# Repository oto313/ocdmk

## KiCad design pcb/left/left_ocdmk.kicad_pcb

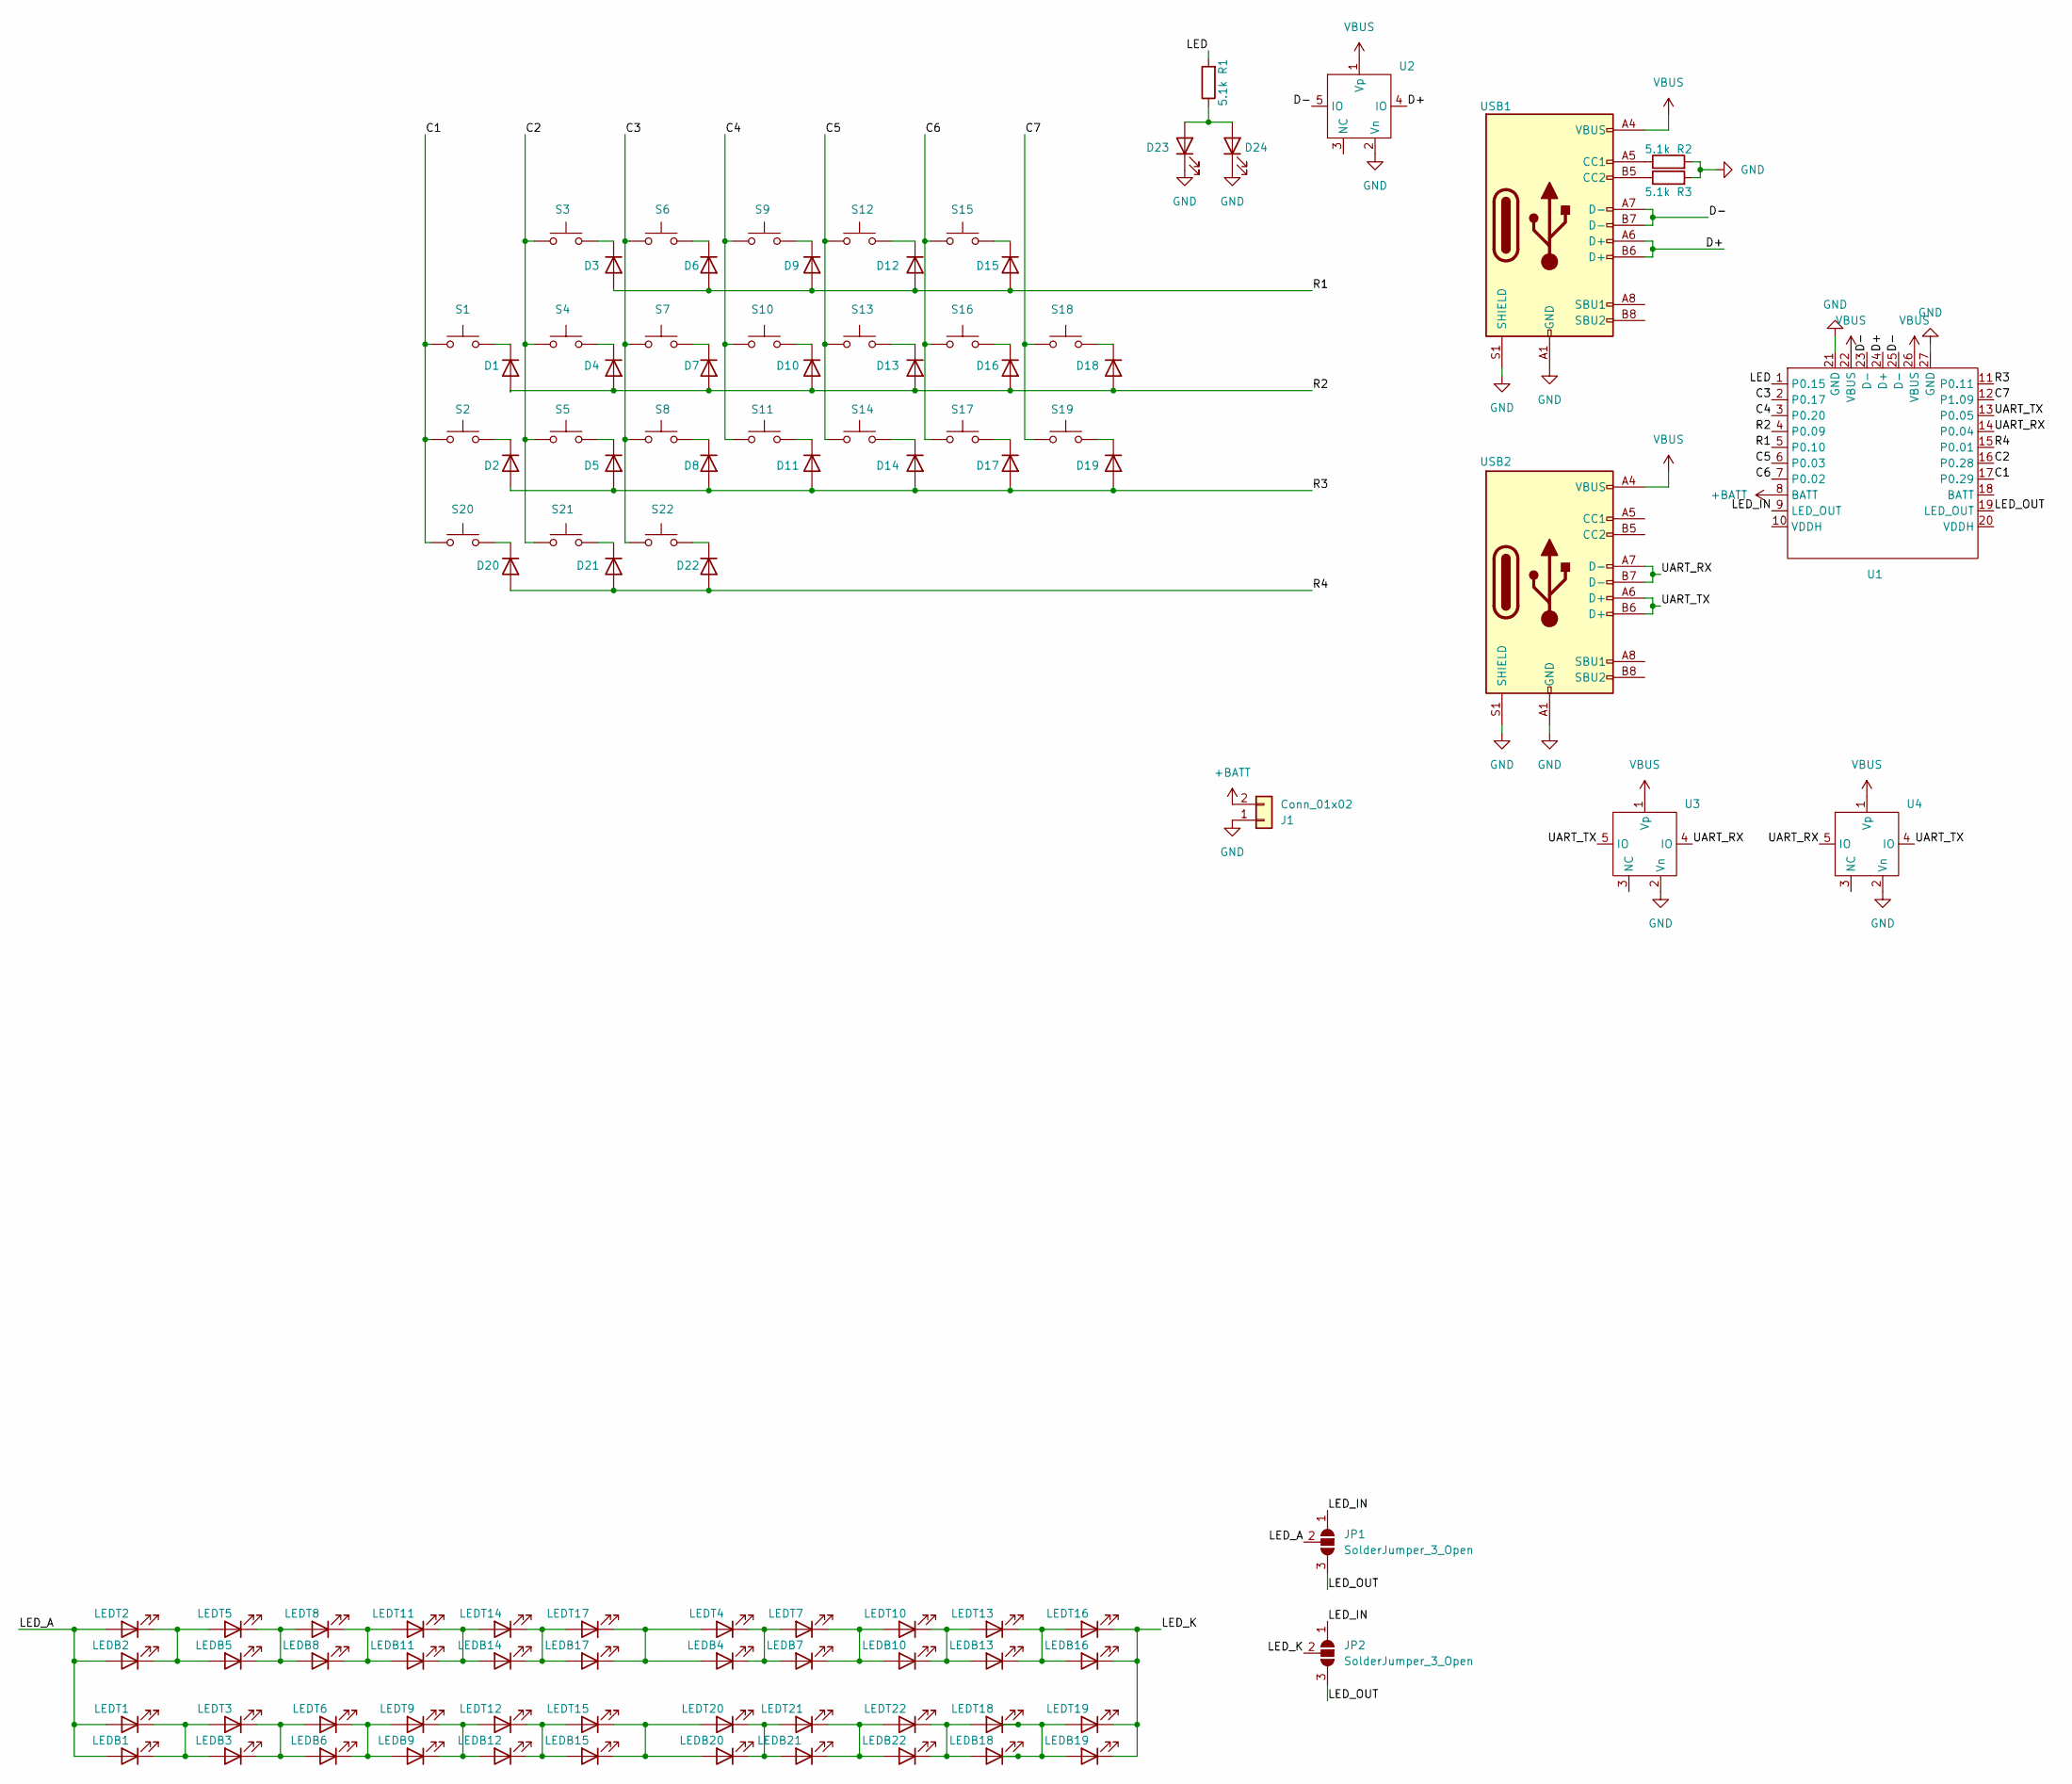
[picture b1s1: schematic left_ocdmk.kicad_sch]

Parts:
D1, D2, D3, D4, D5, D6, D7, D8, D9, D10, D11, D12, D13, D14, D15, D16, D17, D18, D19, D20, D21, D22: diode_tht_sod123_reversible
D23, D24: LED; D_0603_1608Metric
J1: Conn_01x02; JST_PH_S2B-PH-K_1x02_P2.00mm_Horizontal
JP1, JP2: SolderJumper_3_Open; SolderJumper-3_P2.0mm_Open_TrianglePad1.0x1.5mm_NumberLabels
LEDB1, LEDB2, LEDB3, LEDB4, LEDB5, LEDB6, LEDB7, LEDB8, LEDB9, LEDB10, LEDB11, LEDB12, LEDB13, LEDB14, LEDB15, LEDB16, LEDB17, LEDB18, LEDB19, LEDB20, LEDB21, LEDB22: LED_MP-2016-1100-50-90
LEDT1, LEDT2, LEDT3, LEDT4, LEDT5, LEDT6, LEDT7, LEDT8, LEDT9, LEDT10, LEDT11, LEDT12, LEDT13, LEDT14, LEDT15, LEDT16, LEDT17, LEDT18, LEDT19, LEDT20, LEDT21, LEDT22: LED_MP-2016-1100-50-90
R1, R2, R3: 5.1k; R_0603_1608Metric
S1, S2, S3, S4, S5, S6, S7, S8, S9, S10, S11, S12, S13, S14, S15, S16, S17, S18, S19, S20, S21, S22: switch_gateron_ks27_ks33_reversible
U1: ocdmk_core
U2, U3, U4: SOT-553
USB1: USB_C_Receptacle_USB2.0_16P; 12402012E212A_AMP
USB2: USB_C_Receptacle_USB2.0_16P; 12402012E212A_AMP_reversible

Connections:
+BATT: J1.2, U1.8 (BATT)
/C1: S1.1, S2.1, S20.1, U1.17 (P0.29)
/C2: S3.1, S4.1, S5.1, S21.1, U1.16 (P0.28)
/C3: S6.1, S7.1, S8.1, S22.1, U1.2 (P0.17)
/C4: S9.1, S10.1, S11.1, U1.3 (P0.20)
/C5: S12.1, S13.1, S14.1, U1.6 (P0.03)
/C6: S15.1, S16.1, S17.1, U1.7 (P0.02)
/C7: S18.1, S19.1, U1.12 (P1.09)
/D+: U1.24 (D+), U2.4 (IO), USB1.A6 (D+), USB1.B6 (D+)
/D-: U1.23 (D-), U1.25 (D-), U2.5 (IO), USB1.A7 (D-), USB1.B7 (D-)
/LED: R1.2, U1.1 (P0.15)
/LED_A: JP1.2 (C), LEDB1.2 (A), LEDB2.2 (A), LEDT1.2 (A), LEDT2.2 (A)
/LED_IN: JP1.1 (A), JP2.1 (A), U1.9 (LED_OUT)
/LED_K: JP2.2 (C), LEDB16.1 (K), LEDB19.1 (K), LEDT16.1 (K), LEDT19.1 (K)
/LED_OUT: JP1.3 (B), JP2.3 (B), U1.19 (LED_OUT)
/R1: D3.2 (A), D6.2 (A), D9.2 (A), D12.2 (A), D15.2 (A), U1.5 (P0.10)
/R2: D1.2 (A), D4.2 (A), D7.2 (A), D10.2 (A), D13.2 (A), D16.2 (A), D18.2 (A), U1.4 (P0.09)
/R3: D2.2 (A), D5.2 (A), D8.2 (A), D11.2 (A), D14.2 (A), D17.2 (A), D19.2 (A), U1.11 (P0.11)
/R4: D20.2 (A), D21.2 (A), D22.2 (A), U1.15 (P0.01)
/UART_RX: U1.14 (P0.04), U3.4 (IO), U4.5 (IO), USB2.A7 (D-), USB2.B7 (D-)
/UART_TX: U1.13 (P0.05), U3.5 (IO), U4.4 (IO), USB2.A6 (D+), USB2.B6 (D+)
GND: D23.1 (K), D24.1 (K), J1.1, R2.2, R3.2, U1.21 (GND), U1.27 (GND), U2.2 (Vn), U3.2 (Vn), U4.2 (Vn), USB1.A1 (GND), USB1.A12 (GND), USB1.B1 (GND), USB1.B12 (GND), USB1.S1 (SHIELD), USB2.A1 (GND), USB2.A12 (GND), USB2.B1 (GND), USB2.B12 (GND), USB2.S1 (SHIELD)
unnamed: D1.1 (K), S1.2
unnamed: D2.1 (K), S2.2
unnamed: D3.1 (K), S3.2
unnamed: D4.1 (K), S4.2
unnamed: D5.1 (K), S5.2
unnamed: D6.1 (K), S6.2
unnamed: D7.1 (K), S7.2
unnamed: D8.1 (K), S8.2
unnamed: D9.1 (K), S9.2
unnamed: D10.1 (K), S10.2
unnamed: D11.1 (K), S11.2
unnamed: D12.1 (K), S12.2
unnamed: D13.1 (K), S13.2
unnamed: D14.1 (K), S14.2
unnamed: D15.1 (K), S15.2
unnamed: D16.1 (K), S16.2
unnamed: D17.1 (K), S17.2
unnamed: D18.1 (K), S18.2
unnamed: D19.1 (K), S19.2
unnamed: D20.1 (K), S20.2
unnamed: D21.1 (K), S21.2
unnamed: D22.1 (K), S22.2
unnamed: D23.2 (A), D24.2 (A), R1.1
unnamed: LEDB1.1 (K), LEDB3.2 (A), LEDT1.1 (K), LEDT3.2 (A)
unnamed: LEDB2.1 (K), LEDB5.2 (A), LEDT2.1 (K), LEDT5.2 (A)
unnamed: LEDB3.1 (K), LEDB6.2 (A), LEDT3.1 (K), LEDT6.2 (A)
unnamed: LEDB4.1 (K), LEDB7.2 (A), LEDT4.1 (K), LEDT7.2 (A)
unnamed: LEDB5.1 (K), LEDB8.2 (A), LEDT5.1 (K), LEDT8.2 (A)
unnamed: LEDB6.1 (K), LEDB9.2 (A), LEDT6.1 (K), LEDT9.2 (A)
unnamed: LEDB7.1 (K), LEDB10.2 (A), LEDT7.1 (K), LEDT10.2 (A)
unnamed: LEDB10.1 (K), LEDB13.2 (A), LEDT10.1 (K), LEDT13.2 (A)
unnamed: LEDB8.1 (K), LEDB11.2 (A), LEDT8.1 (K), LEDT11.2 (A)
unnamed: LEDB11.1 (K), LEDB14.2 (A), LEDT11.1 (K), LEDT14.2 (A)
unnamed: LEDB9.1 (K), LEDB12.2 (A), LEDT9.1 (K), LEDT12.2 (A)
unnamed: LEDB12.1 (K), LEDB15.2 (A), LEDT12.1 (K), LEDT15.2 (A)
unnamed: LEDB13.1 (K), LEDB16.2 (A), LEDT13.1 (K), LEDT16.2 (A)
unnamed: LEDB14.1 (K), LEDB17.2 (A), LEDT14.1 (K), LEDT17.2 (A)
unnamed: LEDB15.1 (K), LEDB20.2 (A), LEDT15.1 (K), LEDT20.2 (A)
unnamed: LEDB4.2 (A), LEDB17.1 (K), LEDT4.2 (A), LEDT17.1 (K)
unnamed: LEDB18.2 (A), LEDB22.1 (K), LEDT18.2 (A), LEDT22.1 (K)
unnamed: LEDB18.1 (K), LEDB19.2 (A), LEDT18.1 (K), LEDT19.2 (A)
unnamed: LEDB20.1 (K), LEDB21.2 (A), LEDT20.1 (K), LEDT21.2 (A)
unnamed: LEDB21.1 (K), LEDB22.2 (A), LEDT21.1 (K), LEDT22.2 (A)
unnamed: R2.1, USB1.A5 (CC1)
unnamed: R3.1, USB1.B5 (CC2)
VBUS: U1.22 (VBUS), U1.26 (VBUS), U2.1 (Vp), U3.1 (Vp), U4.1 (Vp), USB1.A4 (VBUS), USB1.A9 (VBUS), USB1.B4 (VBUS), USB1.B9 (VBUS), USB2.A4 (VBUS), USB2.A9 (VBUS), USB2.B4 (VBUS), USB2.B9 (VBUS)

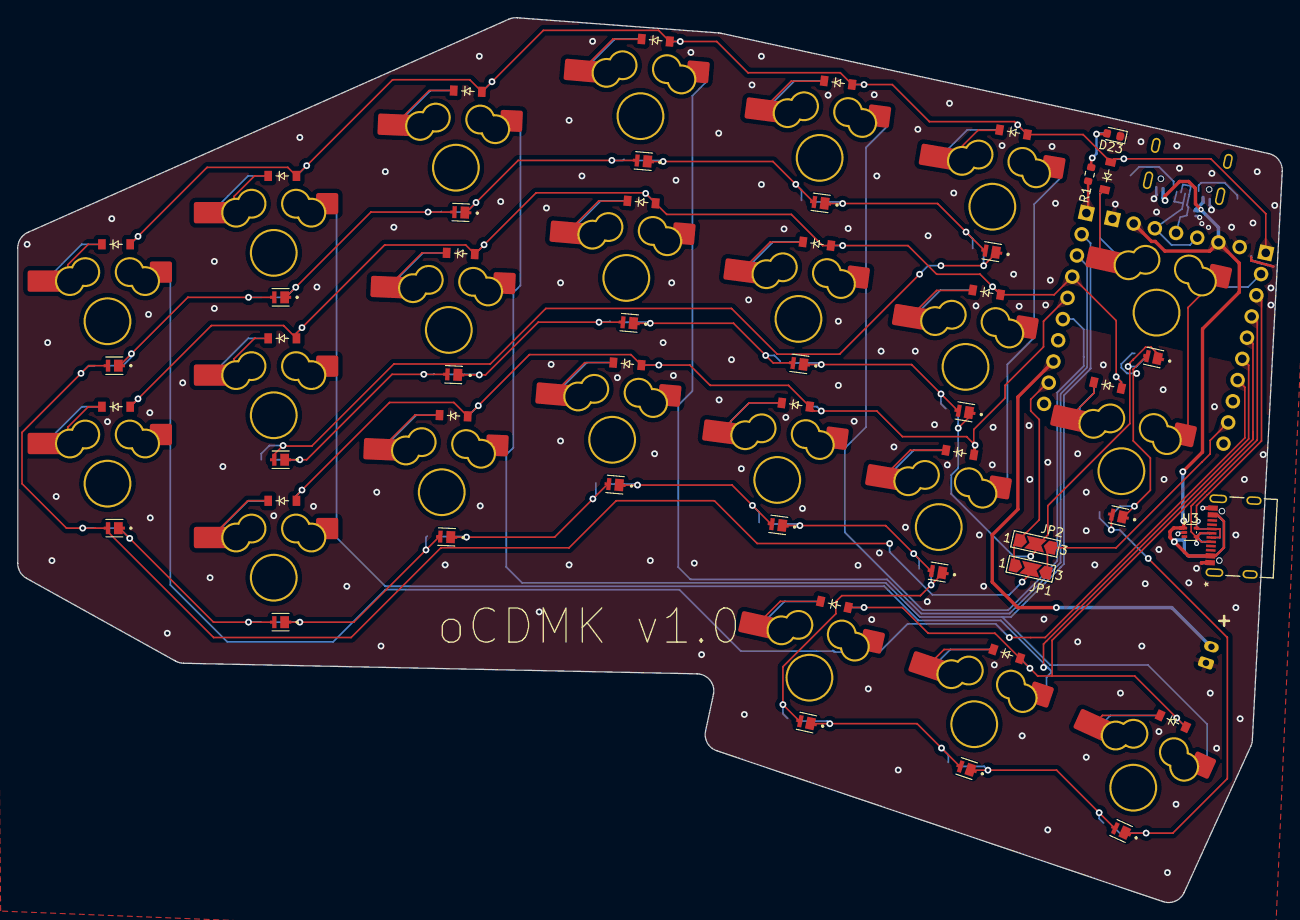
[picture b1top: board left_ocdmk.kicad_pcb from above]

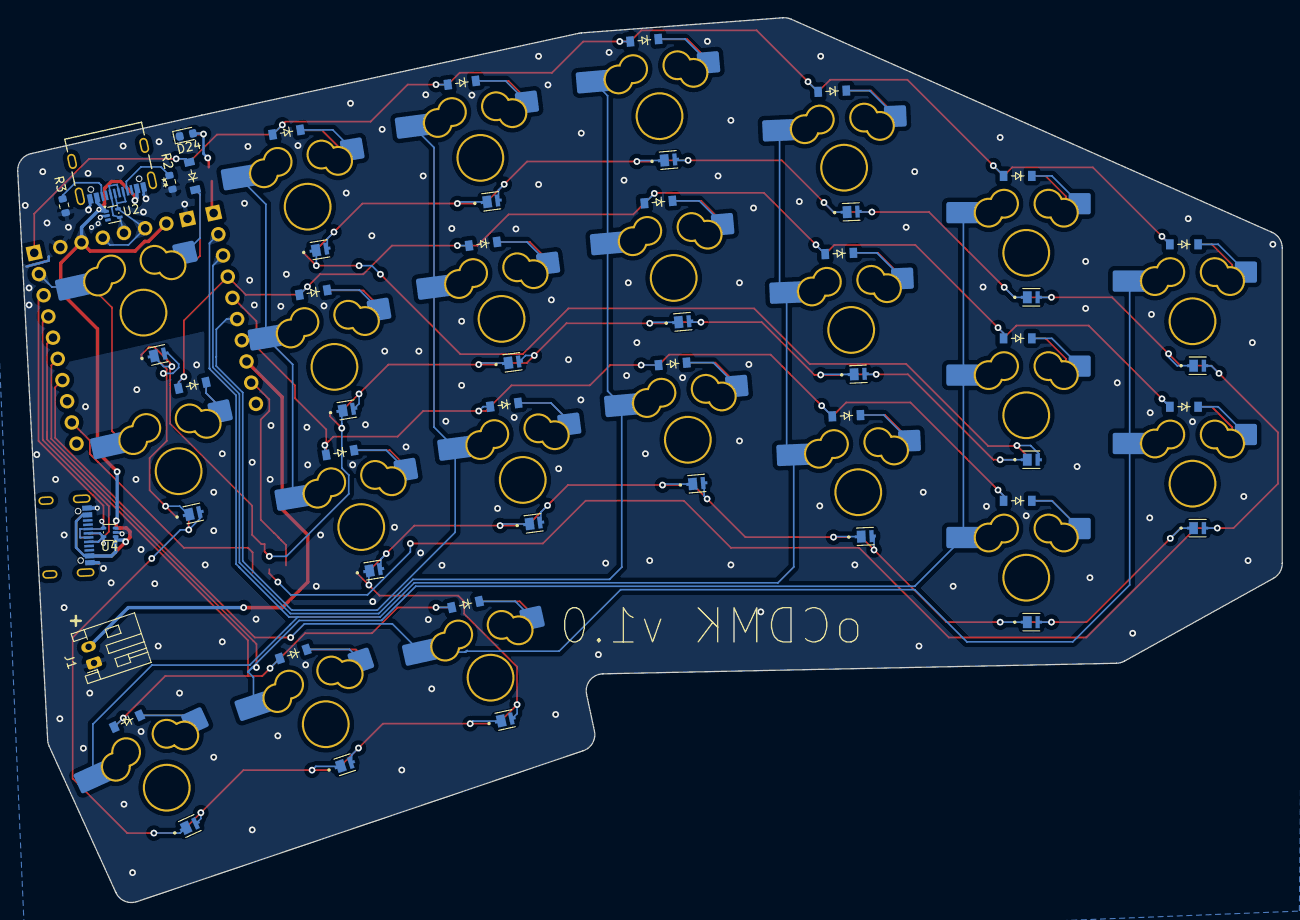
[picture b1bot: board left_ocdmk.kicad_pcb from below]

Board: 2 copper layers, 147.9 x 103.5 mm, 102 parts (51 on the bottom side), 68 nets.

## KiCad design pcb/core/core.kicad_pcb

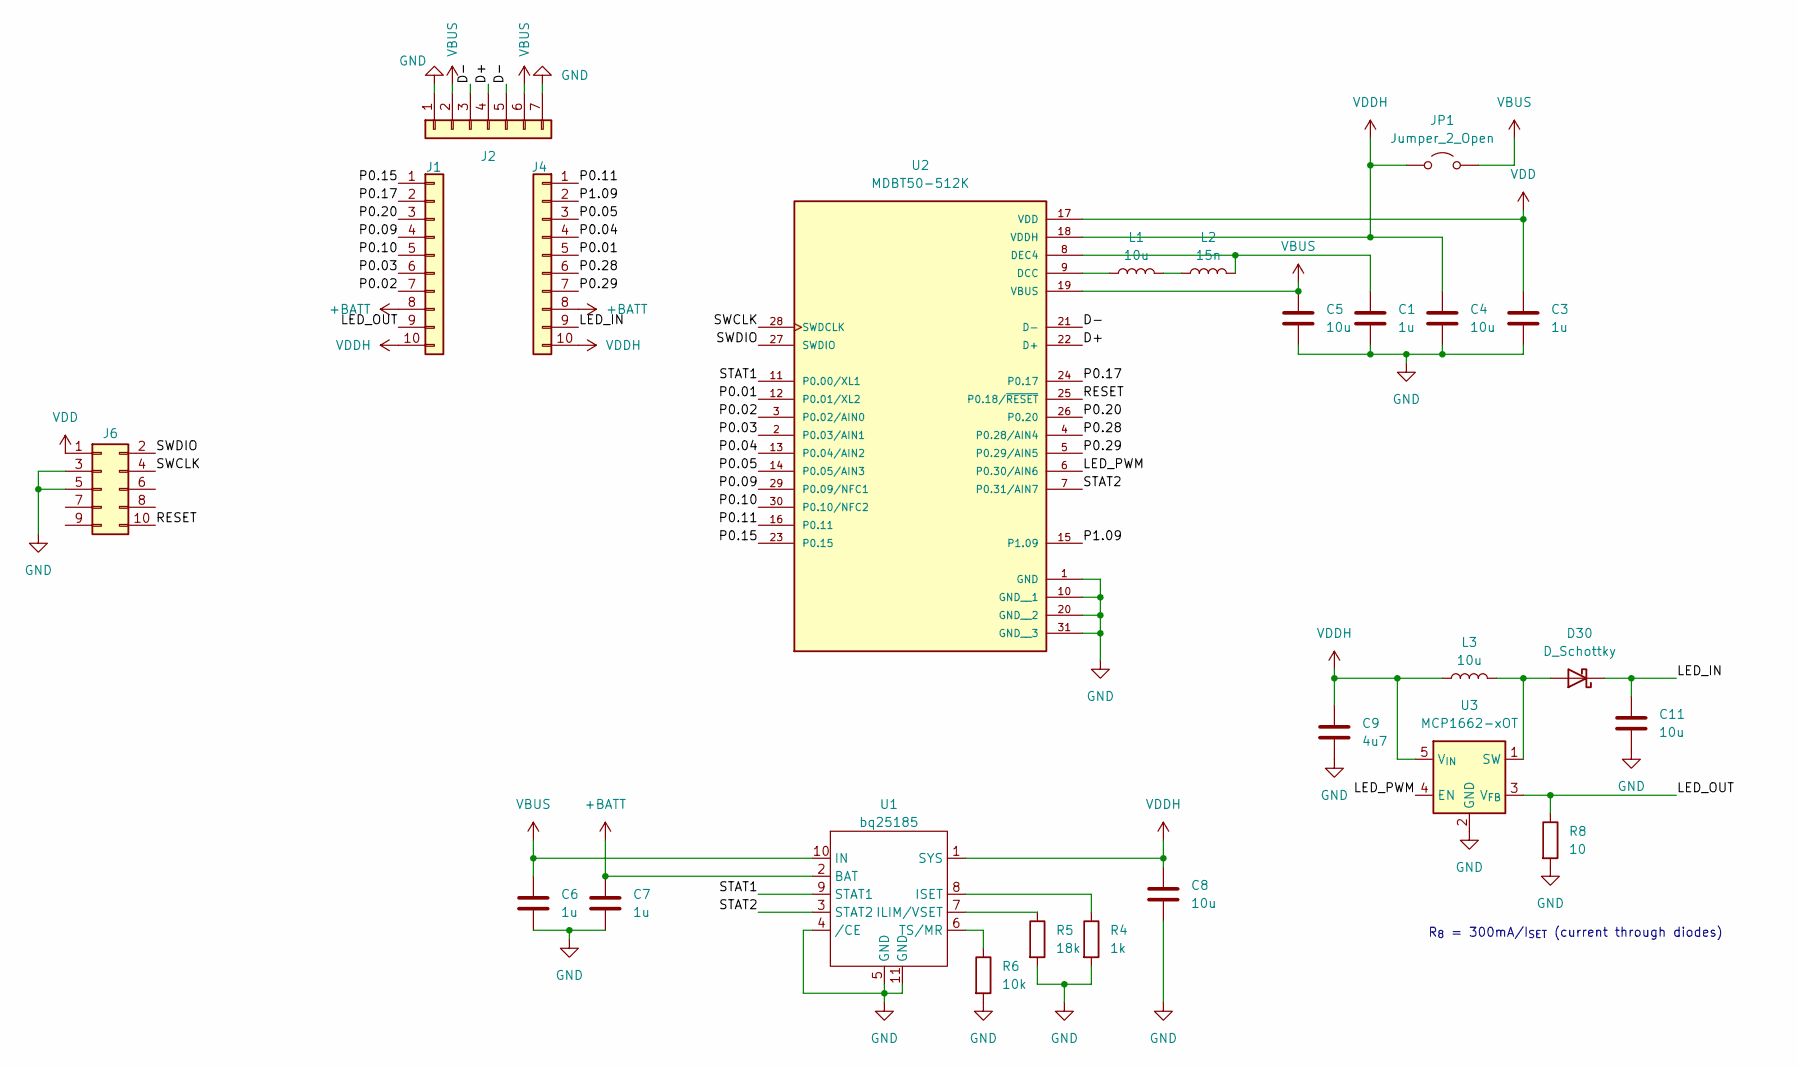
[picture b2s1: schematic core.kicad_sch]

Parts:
C1, C3, C6, C7: 1u; C_0603_1608Metric
C4, C5, C8: 10u; C_0603_1608Metric
C9: 4u7; C_0603_1608Metric
C11: 10u; C_1206_3216Metric
D30: D_Schottky; D_SOD-123
J1, J4: Conn_01x10; PinHeader_1x10_P2.54mm_Vertical
J2: Conn_01x07; PinHeader_1x07_P2.54mm_Vertical
J6: Conn_02x05_Odd_Even; PinHeader_2x05_P1.27mm_Vertical
JP1: Jumper_2_Open; SolderJumper-2_P1.3mm_Open_TrianglePad1.0x1.5mm
L1: 10u; L_0805_2012Metric
L2: 15n; L_0603_1608Metric
L3: 10u; L_0603_1608Metric
R4: 1k; R_0603_1608Metric
R5: 18k; R_0603_1608Metric
R6: 10k; R_0603_1608Metric
R8: 10; R_0603_1608Metric
U1: bq25185; SON50P250X250X80-11N
U2: MDBT50-512K; XCVR_MDBT50-512K; PARTREV B
U3: MCP1662-xOT; SOT-23-5

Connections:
+BATT: C7.1, J1.8, J4.8, U1.2 (BAT)
/D+: J2.4, U2.22 (D+)
/D-: J2.3, J2.5, U2.21 (D-)
/LED_IN: C11.1, D30.1 (K), J4.9
/LED_OUT: J1.9, R8.1, U3.3 (V_{FB})
/LED_PWM: U2.6 (P0.30/AIN6), U3.4 (EN)
/P0.01: J4.5, U2.12 (P0.01/XL2)
/P0.02: J1.7, U2.3 (P0.02/AIN0)
/P0.03: J1.6, U2.2 (P0.03/AIN1)
/P0.04: J4.4, U2.13 (P0.04/AIN2)
/P0.05: J4.3, U2.14 (P0.05/AIN3)
/P0.09: J1.4, U2.29 (P0.09/NFC1)
/P0.10: J1.5, U2.30 (P0.10/NFC2)
/P0.11: J4.1, U2.16 (P0.11)
/P0.15: J1.1, U2.23 (P0.15)
/P0.17: J1.2, U2.24 (P0.17)
/P0.20: J1.3, U2.26 (P0.20)
/P0.28: J4.6, U2.4 (P0.28/AIN4)
/P0.29: J4.7, U2.5 (P0.29/AIN5)
/P1.09: J4.2, U2.15 (P1.09)
/RESET: J6.10, U2.25 (P0.18/~RESET)
/STAT1: U1.9 (STAT1), U2.11 (P0.00/XL1)
/STAT2: U1.3 (STAT2), U2.7 (P0.31/AIN7)
/SWCLK: J6.4, U2.28 (SWDCLK)
/SWDIO: J6.2, U2.27 (SWDIO)
GND: C1.2, C3.2, C4.2, C5.2, C6.2, C7.2, C8.2, C9.2, C11.2, J2.1, J2.7, J6.3, J6.5, R4.2, R5.2, R6.2, R8.2, U1.4 (/CE), U1.5 (GND), U1.11 (GND), U2.1 (GND), U2.10 (GND__1), U2.20 (GND__2), U2.31 (GND__3), U3.2 (GND)
unnamed: D30.2 (A), L3.2, U3.1 (SW)
unnamed: L1.2, L2.1
unnamed: R5.1, U1.7 (ILIM/VSET)
unnamed: R4.1, U1.8 (ISET)
unnamed: R6.1, U1.6 (TS/MR)
unnamed: L1.1, U2.9 (DCC)
unnamed: C1.1, L2.2, U2.8 (DEC4)
VBUS: C5.1, C6.1, J2.2, J2.6, JP1.2 (B), U1.10 (IN), U2.19 (VBUS)
VDD: C3.1, J6.1, U2.17 (VDD)
VDDH: C4.1, C8.1, C9.1, J1.10, J4.10, JP1.1 (A), L3.1, U1.1 (SYS), U2.18 (VDDH), U3.5 (V_{IN})

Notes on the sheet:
R_{8} = 300mA/I_{SET} (current through diodes)

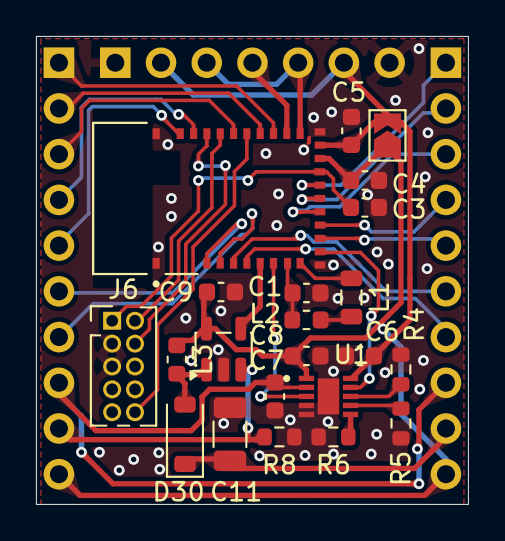
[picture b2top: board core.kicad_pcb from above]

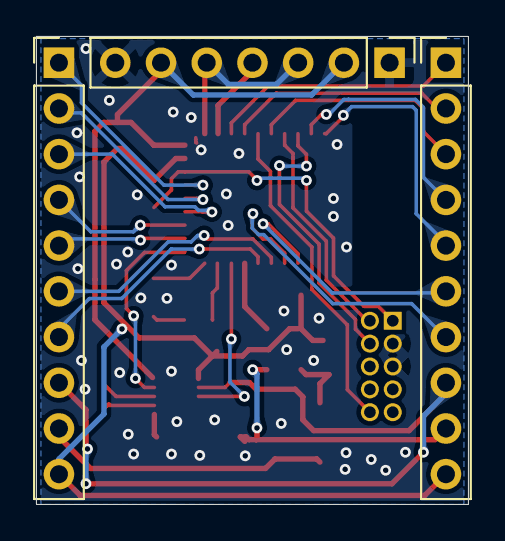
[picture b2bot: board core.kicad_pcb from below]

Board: 2 copper layers, 24.0 x 26.0 mm, 25 parts (3 on the bottom side), 36 nets.

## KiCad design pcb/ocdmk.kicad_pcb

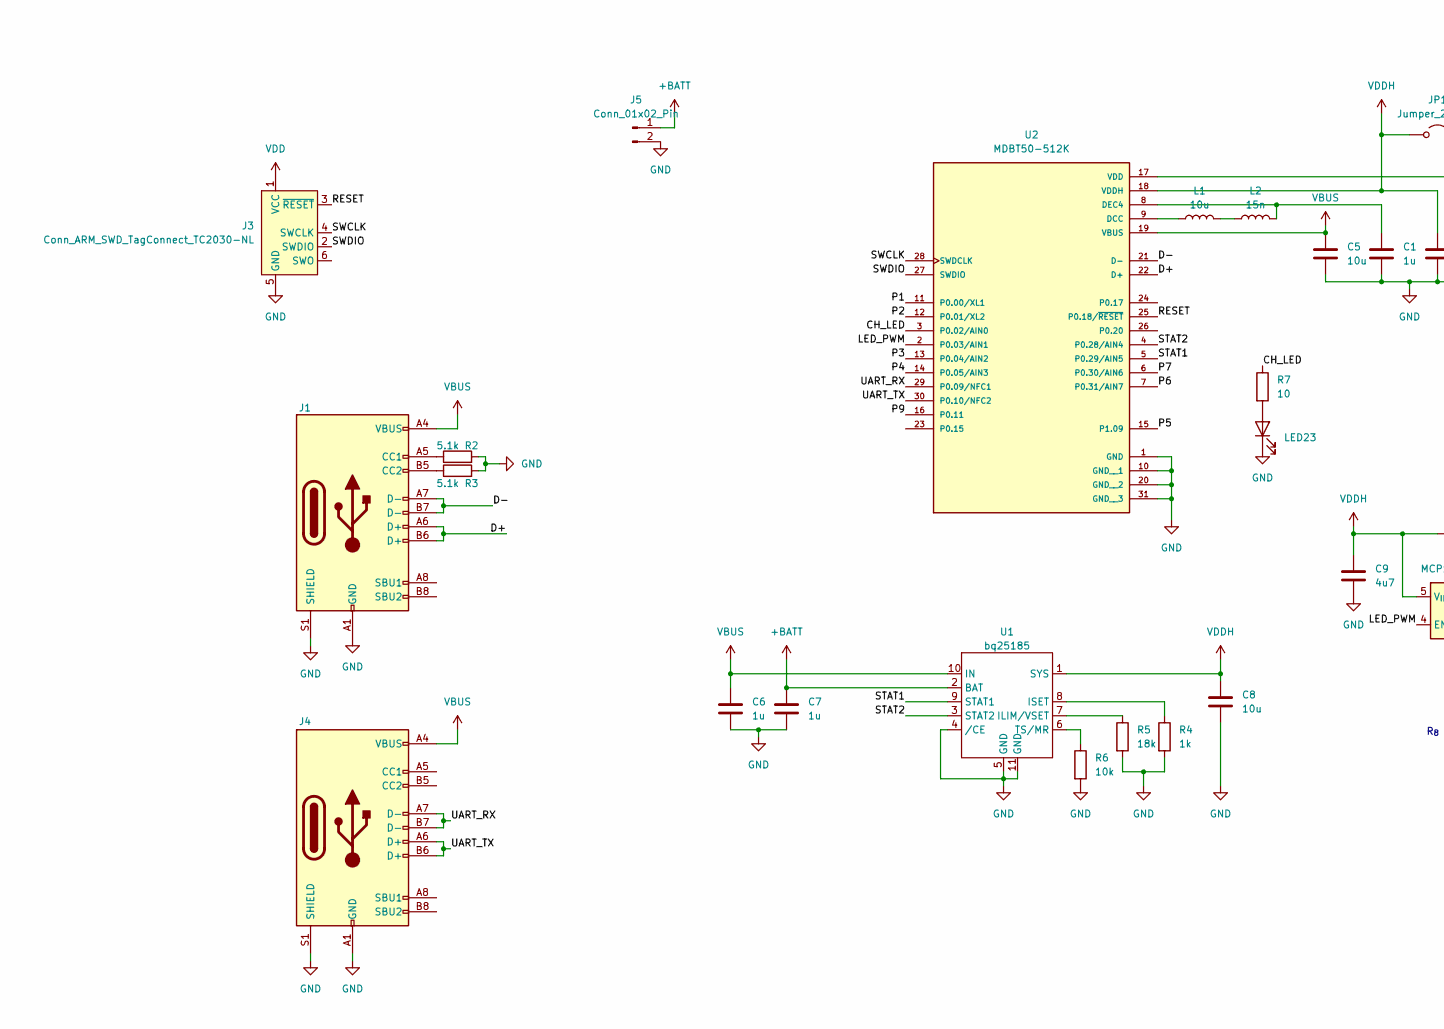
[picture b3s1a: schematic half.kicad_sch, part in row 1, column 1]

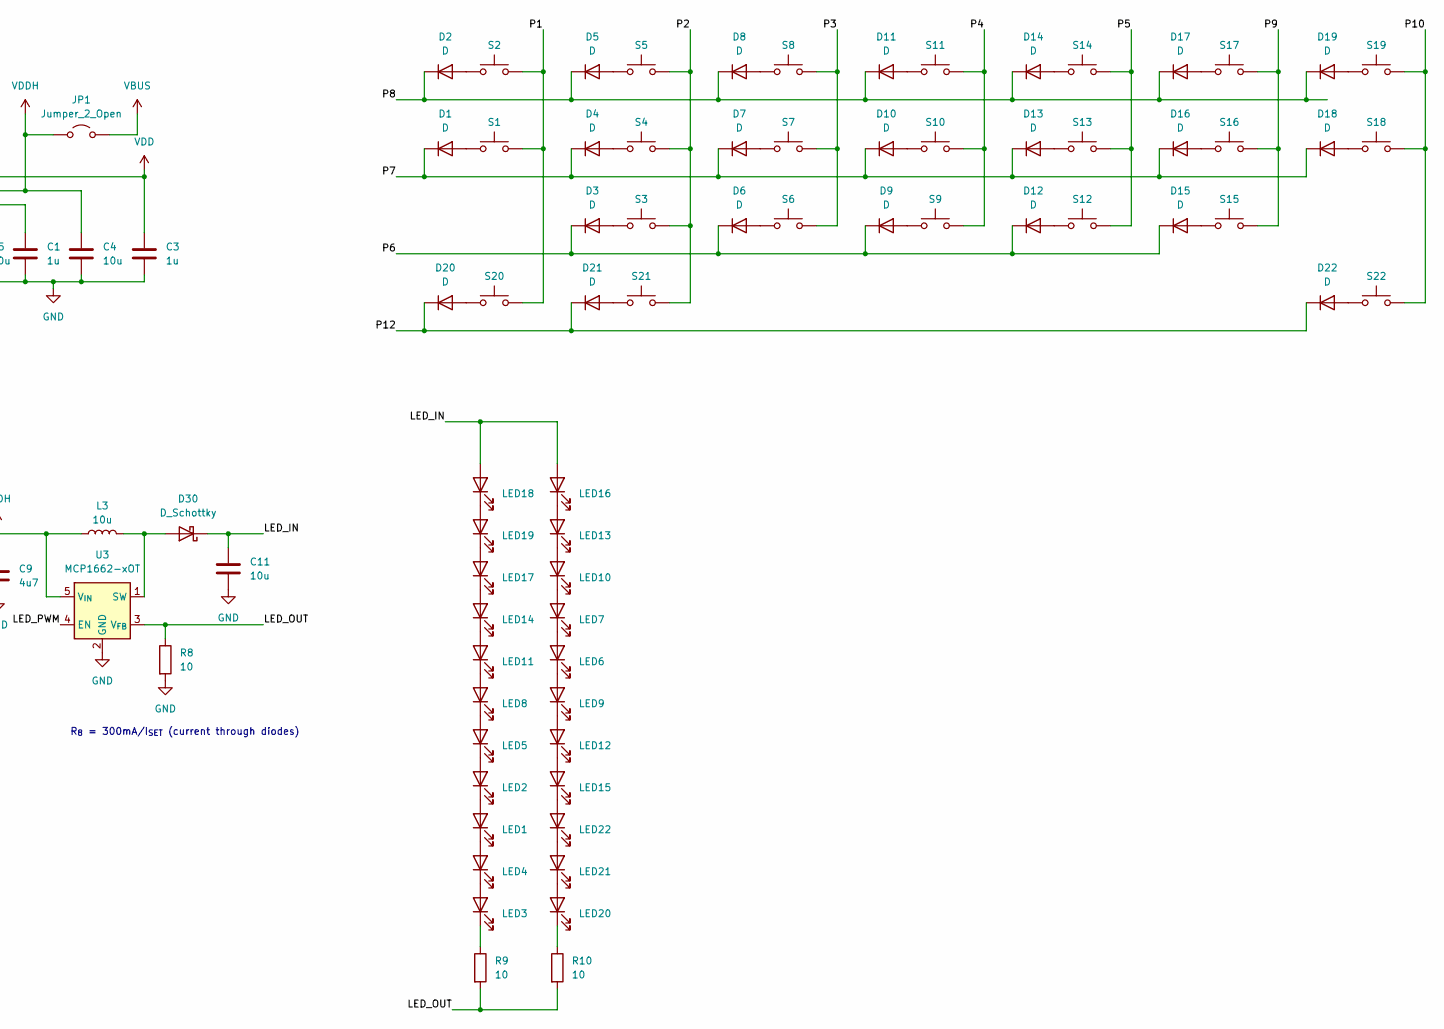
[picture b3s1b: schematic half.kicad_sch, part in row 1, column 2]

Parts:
C1, C3, C6, C7: 1u; C_0603_1608Metric
C4, C5, C8: 10u; C_0603_1608Metric
C9: 4u7; C_0603_1608Metric
C11: 10u; C_1206_3216Metric
D1, D2, D3, D4, D5, D6, D7, D8, D9, D10, D11, D12, D13, D14, D15, D16, D17, D18, D19, D20, D21, D22: D; D_SOD-123
D30: D_Schottky; D_SOD-123
J1, J4: USB_C_Receptacle_USB2.0_16P; 12402012E212A_AMP
J3: Conn_ARM_SWD_TagConnect_TC2030-NL; Tag-Connect_TC2030-IDC-FP_2x03_P1.27mm_Vertical
J5: Conn_01x02_Pin; JST_PH_S2B-PH-K_1x02_P2.00mm_Horizontal
JP1: Jumper_2_Open; SolderJumper-2_P1.3mm_Open_TrianglePad1.0x1.5mm
L1: 10u; L_0805_2012Metric
L2: 15n; L_0603_1608Metric
L3: 10u; L_0603_1608Metric
LED1, LED2, LED3, LED4, LED5, LED6, LED7, LED8, LED9, LED10, LED11, LED12, LED13, LED14, LED15, LED16, LED17, LED18, LED19, LED20, LED21, LED22: LED; LED_MP-2016-1100-50-90
LED23: LED; LED_0603_1608Metric
R2, R3: 5.1k; R_0603_1608Metric
R4: 1k; R_0603_1608Metric
R5: 18k; R_0603_1608Metric
R6: 10k; R_0603_1608Metric
R7, R8, R9, R10: 10; R_0603_1608Metric
S1, S2, S3, S4, S5, S6, S7, S8, S9, S10, S11, S12, S13, S14, S15, S16, S17, S18, S19, S20, S21, S22: SW_Push; switch_gateron_ks27_ks33
U1: bq25185; SON50P250X250X80-11N
U2: MDBT50-512K; XCVR_MDBT50-512K; PARTREV B
U3: MCP1662-xOT; SOT-23-5

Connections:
+BATT: C7.1, J5.1, U1.2 (BAT)
/Untitled Sheet/CH_LED: R7.1, U2.3 (P0.02/AIN0)
/Untitled Sheet/D+: J1.A6 (D+), J1.B6 (D+), U2.22 (D+)
/Untitled Sheet/D-: J1.A7 (D-), J1.B7 (D-), U2.21 (D-)
/Untitled Sheet/LED_IN: C11.1, D30.1 (K), LED16.2 (A), LED18.2 (A)
/Untitled Sheet/LED_OUT: R8.1, R9.2, R10.2, U3.3 (V_{FB})
/Untitled Sheet/LED_PWM: U2.2 (P0.03/AIN1), U3.4 (EN)
/Untitled Sheet/P1: S1.1, S2.1, S20.1, U2.11 (P0.00/XL1)
/Untitled Sheet/P2: S3.1, S4.1, S5.1, S21.1, U2.12 (P0.01/XL2)
/Untitled Sheet/P3: S6.1, S7.1, S8.1, U2.13 (P0.04/AIN2)
/Untitled Sheet/P4: S9.1, S10.1, S11.1, U2.14 (P0.05/AIN3)
/Untitled Sheet/P5: S12.1, S13.1, S14.1, U2.15 (P1.09)
/Untitled Sheet/P6: D3.1 (K), D6.1 (K), D9.1 (K), D12.1 (K), D15.1 (K), U2.7 (P0.31/AIN7)
/Untitled Sheet/P7: D1.1 (K), D4.1 (K), D7.1 (K), D10.1 (K), D13.1 (K), D16.1 (K), D18.1 (K), U2.6 (P0.30/AIN6)
/Untitled Sheet/P8: D2.1 (K), D5.1 (K), D8.1 (K), D11.1 (K), D14.1 (K), D17.1 (K), D19.1 (K)
/Untitled Sheet/P9: S15.1, S16.1, S17.1, U2.16 (P0.11)
/Untitled Sheet/P10: S18.1, S19.1, S22.1
/Untitled Sheet/P12: D20.1 (K), D21.1 (K), D22.1 (K)
/Untitled Sheet/RESET: J3.3 (~RESET), U2.25 (P0.18/~RESET)
/Untitled Sheet/STAT1: U1.9 (STAT1), U2.5 (P0.29/AIN5)
/Untitled Sheet/STAT2: U1.3 (STAT2), U2.4 (P0.28/AIN4)
/Untitled Sheet/SWCLK: J3.4 (SWCLK), U2.28 (SWDCLK)
/Untitled Sheet/SWDIO: J3.2 (SWDIO), U2.27 (SWDIO)
/Untitled Sheet/UART_RX: J4.A7 (D-), J4.B7 (D-), U2.29 (P0.09/NFC1)
/Untitled Sheet/UART_TX: J4.A6 (D+), J4.B6 (D+), U2.30 (P0.10/NFC2)
GND: C1.2, C3.2, C4.2, C5.2, C6.2, C7.2, C8.2, C9.2, C11.2, J1.A1 (GND), J1.A12 (GND), J1.B1 (GND), J1.B12 (GND), J1.S1 (SHIELD), J3.5 (GND), J4.A1 (GND), J4.A12 (GND), J4.B1 (GND), J4.B12 (GND), J4.S1 (SHIELD), J5.2, LED23.1 (K), R2.2, R3.2, R4.2, R5.2, R6.2, R8.2, U1.4 (/CE), U1.5 (GND), U1.11 (GND), U2.1 (GND), U2.10 (GND__1), U2.20 (GND__2), U2.31 (GND__3), U3.2 (GND)
unnamed: D1.2 (A), S1.2
unnamed: D2.2 (A), S2.2
unnamed: D3.2 (A), S3.2
unnamed: D4.2 (A), S4.2
unnamed: D5.2 (A), S5.2
unnamed: D6.2 (A), S6.2
unnamed: D7.2 (A), S7.2
unnamed: D8.2 (A), S8.2
unnamed: D9.2 (A), S9.2
unnamed: D10.2 (A), S10.2
unnamed: D11.2 (A), S11.2
unnamed: D12.2 (A), S12.2
unnamed: D13.2 (A), S13.2
unnamed: D14.2 (A), S14.2
unnamed: D15.2 (A), S15.2
unnamed: D16.2 (A), S16.2
unnamed: D17.2 (A), S17.2
unnamed: D18.2 (A), S18.2
unnamed: D19.2 (A), S19.2
unnamed: D20.2 (A), S20.2
unnamed: D21.2 (A), S21.2
unnamed: D22.2 (A), S22.2
unnamed: D30.2 (A), L3.2, U3.1 (SW)
unnamed: J1.A5 (CC1), R2.1
unnamed: J1.B5 (CC2), R3.1
unnamed: L1.2, L2.1
unnamed: LED1.2 (A), LED2.1 (K)
unnamed: LED1.1 (K), LED4.2 (A)
unnamed: LED2.2 (A), LED5.1 (K)
unnamed: LED3.2 (A), LED4.1 (K)
unnamed: LED3.1 (K), R9.1
unnamed: LED5.2 (A), LED8.1 (K)
unnamed: LED6.2 (A), LED7.1 (K)
unnamed: LED6.1 (K), LED9.2 (A)
unnamed: LED10.2 (A), LED13.1 (K)
unnamed: LED7.2 (A), LED10.1 (K)
unnamed: LED11.2 (A), LED14.1 (K)
unnamed: LED8.2 (A), LED11.1 (K)
unnamed: LED9.1 (K), LED12.2 (A)
unnamed: LED12.1 (K), LED15.2 (A)
unnamed: LED13.2 (A), LED16.1 (K)
unnamed: LED14.2 (A), LED17.1 (K)
unnamed: LED15.1 (K), LED22.2 (A)
unnamed: LED17.2 (A), LED19.1 (K)
unnamed: LED18.1 (K), LED19.2 (A)
unnamed: LED20.2 (A), LED21.1 (K)
unnamed: LED20.1 (K), R10.1
unnamed: LED21.2 (A), LED22.1 (K)
unnamed: LED23.2 (A), R7.2
unnamed: R5.1, U1.7 (ILIM/VSET)
unnamed: R4.1, U1.8 (ISET)
unnamed: R6.1, U1.6 (TS/MR)
unnamed: L1.1, U2.9 (DCC)
unnamed: C1.1, L2.2, U2.8 (DEC4)
VBUS: C5.1, C6.1, J1.A4 (VBUS), J1.A9 (VBUS), J1.B4 (VBUS), J1.B9 (VBUS), J4.A4 (VBUS), J4.A9 (VBUS), J4.B4 (VBUS), J4.B9 (VBUS), JP1.2 (B), U1.10 (IN), U2.19 (VBUS)
VDD: C3.1, J3.1 (VCC), U2.17 (VDD)
VDDH: C4.1, C8.1, C9.1, JP1.1 (A), L3.1, U1.1 (SYS), U2.18 (VDDH), U3.5 (V_{IN})

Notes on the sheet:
R_{8} = 300mA/I_{SET} (current through diodes)

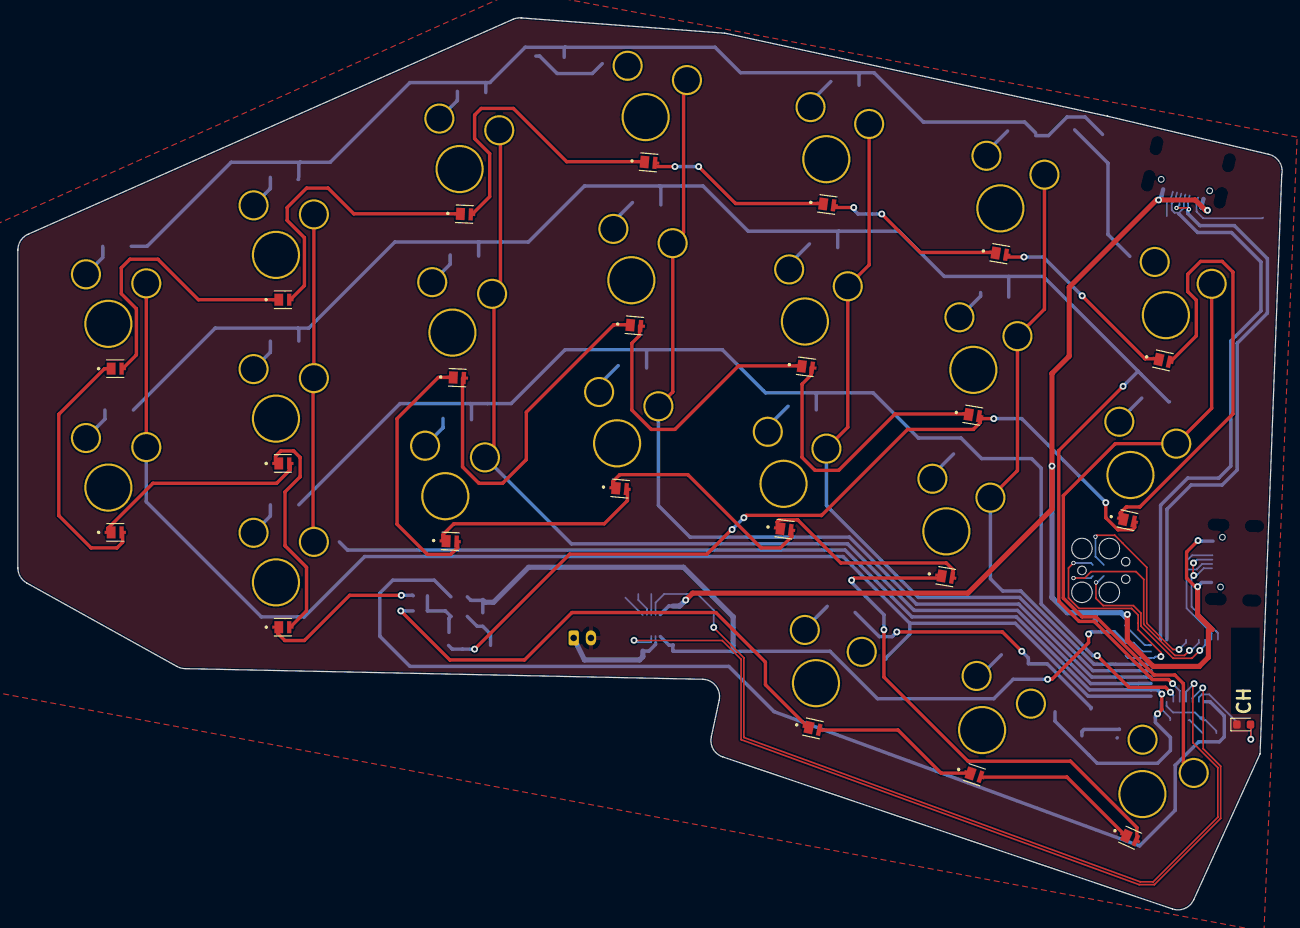
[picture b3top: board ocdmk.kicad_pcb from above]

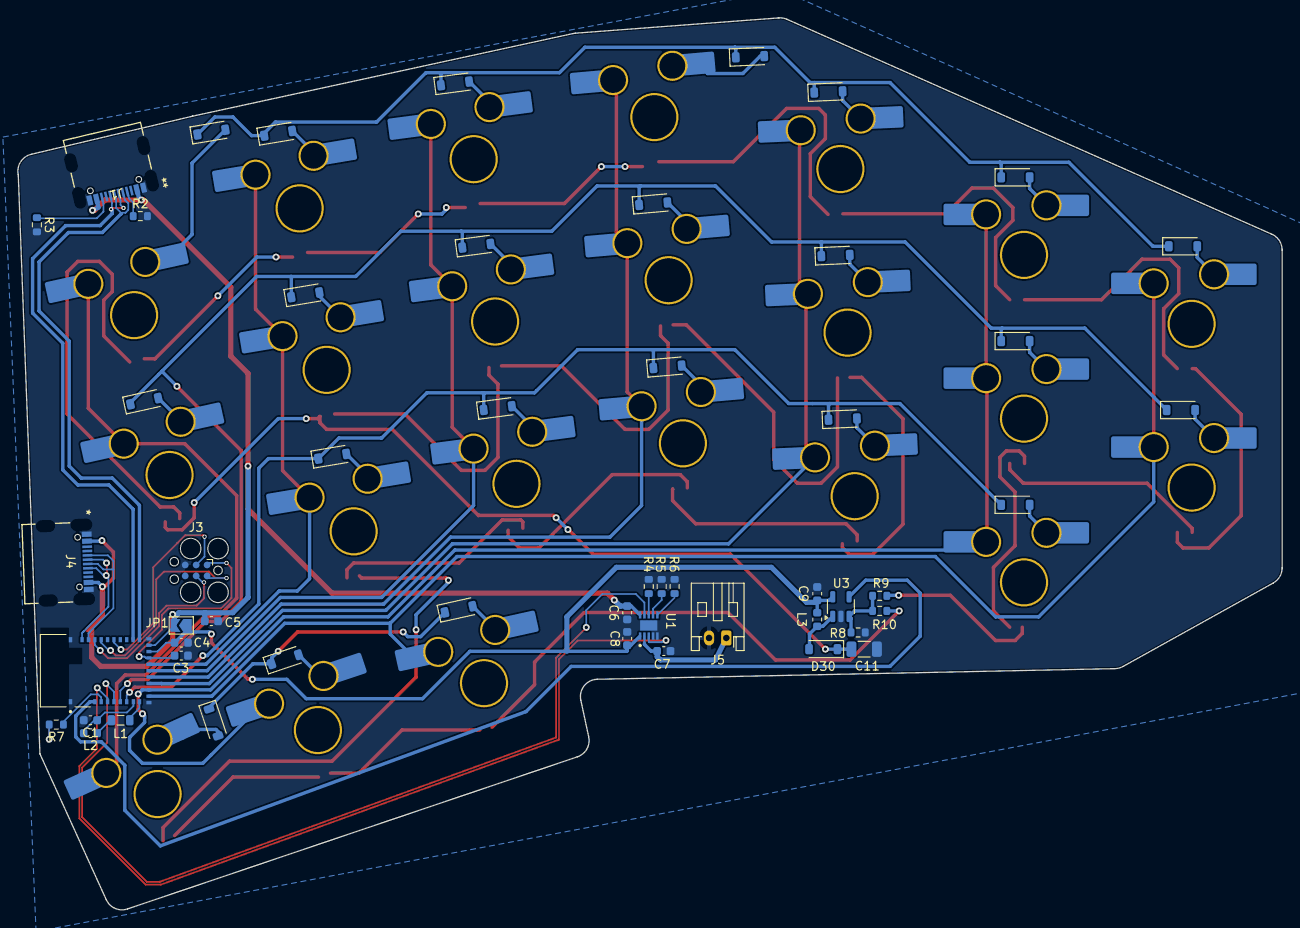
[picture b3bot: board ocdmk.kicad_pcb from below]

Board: 2 copper layers, 146.7 x 103.5 mm, 97 parts (74 on the bottom side), 83 nets.

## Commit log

2025-11-10 Added components
2025-11-12 half completed
2025-11-16 Preparation of mirror
2025-12-11 Finalized reversible design
2025-12-11 Saved
2025-12-17 Some fixes on PCB
2025-12-17 added zmk submodule
